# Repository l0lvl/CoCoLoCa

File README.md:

# CoCoLoCa - MC6847T1 VDG Conversion for CoCo 1 and 2
 
The **CoCoLoCa** allows installation of an MC6847T1/XC80652P in a Radio Shack Colour Computer 1 or 2

This is based on the work of Tony DiStefano as published in the October through December 1986 issues of Rainbow magazine. 

Over the course of two or three articles, Tony explains how to install the new VDG in the Colour Computer, and how to use switches to configure text mode.
This design attempts to cover both the installation and provide jumpers for the text mode settings.

The main PCB (assuming I've interpreted the instructions correctly and failed to make any mistakes) should let you substitute the new MC6847T1/XC80652P VDG in place of the old MC6847. This enables lower case character set (hence the name of this project) as well as a couple of different text mode options. The chip is rather hard to find, but since I have one I thought this would be fun project for #septandy this year.

The main PCB has two fly out lines that have to go to the SAM chip. 

The config plug is installed in place of a 74LS273 that must be removed from the motherboard.  I believe this reconfigures your Coco for some of the data and address pin changes on the new VDG. 

There is an optional SAMTAP board that just lets you easily remove the modification later.

Tony suggests that the wiring for the plug may require a different configuration for CoCo2 models, so expect to see more plugable boards here for those models if that turns out to be the case. I think he also mentioned prizes for sending him the various configuration maps and that he would publish them, but I've come up empty looking for such.

In any case, this design has not been tested so use at your own risk.

Happy #septandy 2022!

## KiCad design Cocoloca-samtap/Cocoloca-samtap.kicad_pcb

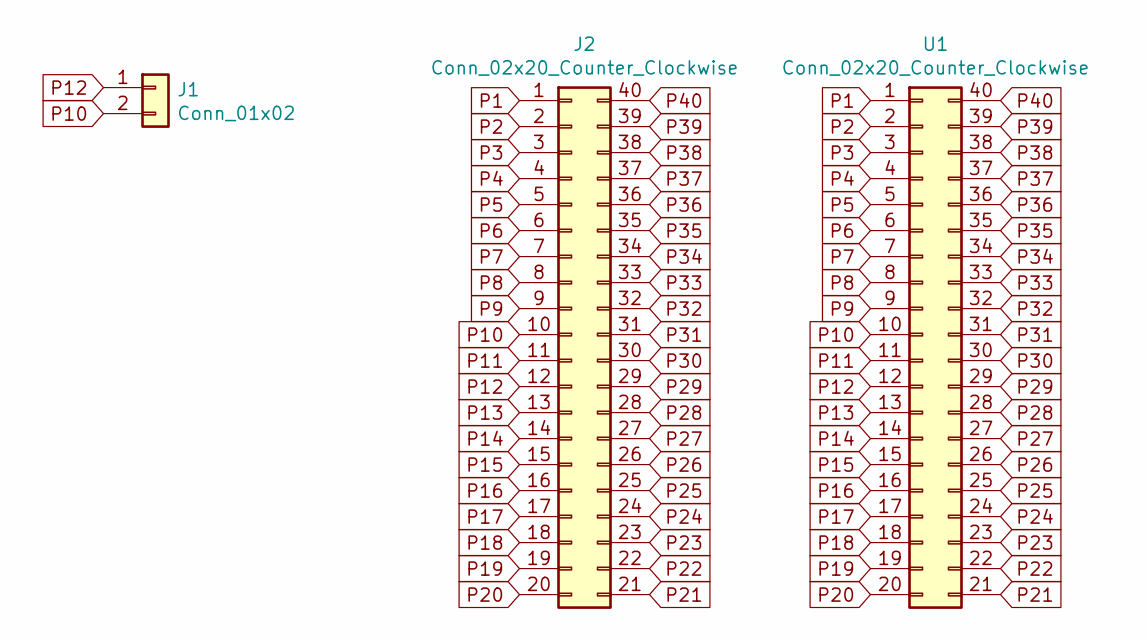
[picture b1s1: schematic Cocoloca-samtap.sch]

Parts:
J1: Conn_01x02; PinHeader_1x02_P2.54mm_Horizontal
J2: Conn_02x20_Counter_Clockwise; DIP-40_W15.24mm_LongPads
U1: Conn_02x20_Counter_Clockwise; DIP-40_W15.24mm_LongPads

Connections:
P1: J2.1, U1.1
P2: J2.2, U1.2
P3: J2.3, U1.3
P4: J2.4, U1.4
P5: J2.5, U1.5
P6: J2.6, U1.6
P7: J2.7, U1.7
P8: J2.8, U1.8
P9: J2.9, U1.9
P10: J1.2, J2.10, U1.10
P11: J2.11, U1.11
P12: J1.1, J2.12, U1.12
P13: J2.13, U1.13
P14: J2.14, U1.14
P15: J2.15, U1.15
P16: J2.16, U1.16
P17: J2.17, U1.17
P18: J2.18, U1.18
P19: J2.19, U1.19
P20: J2.20, U1.20
P21: J2.21, U1.21
P22: J2.22, U1.22
P23: J2.23, U1.23
P24: J2.24, U1.24
P25: J2.25, U1.25
P26: J2.26, U1.26
P27: J2.27, U1.27
P28: J2.28, U1.28
P29: J2.29, U1.29
P30: J2.30, U1.30
P31: J2.31, U1.31
P32: J2.32, U1.32
P33: J2.33, U1.33
P34: J2.34, U1.34
P35: J2.35, U1.35
P36: J2.36, U1.36
P37: J2.37, U1.37
P38: J2.38, U1.38
P39: J2.39, U1.39
P40: J2.40, U1.40

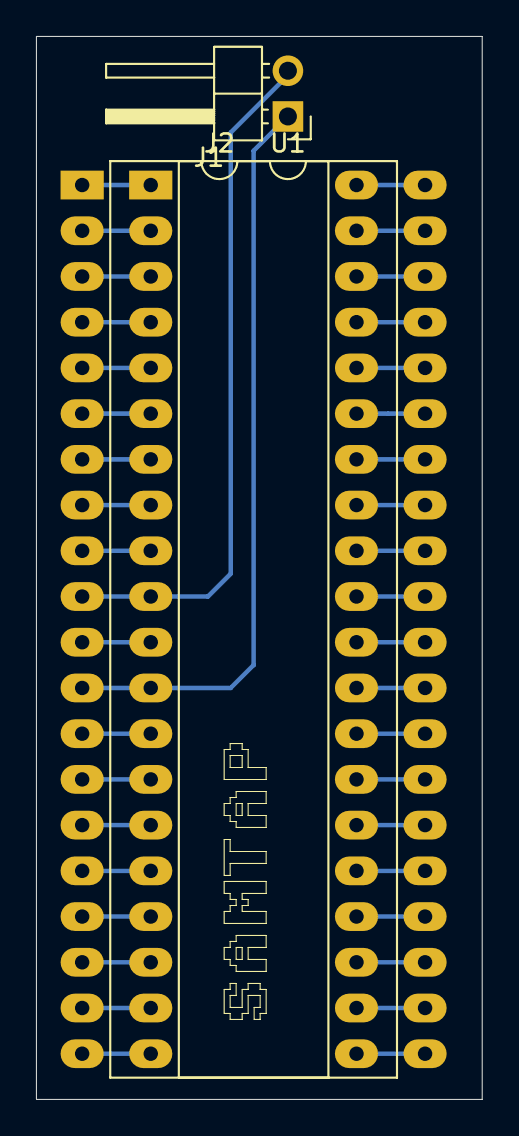
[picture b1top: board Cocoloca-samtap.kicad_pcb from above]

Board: 2 copper layers, 24.8 x 59.1 mm, 3 parts (0 on the bottom side), 40 nets.

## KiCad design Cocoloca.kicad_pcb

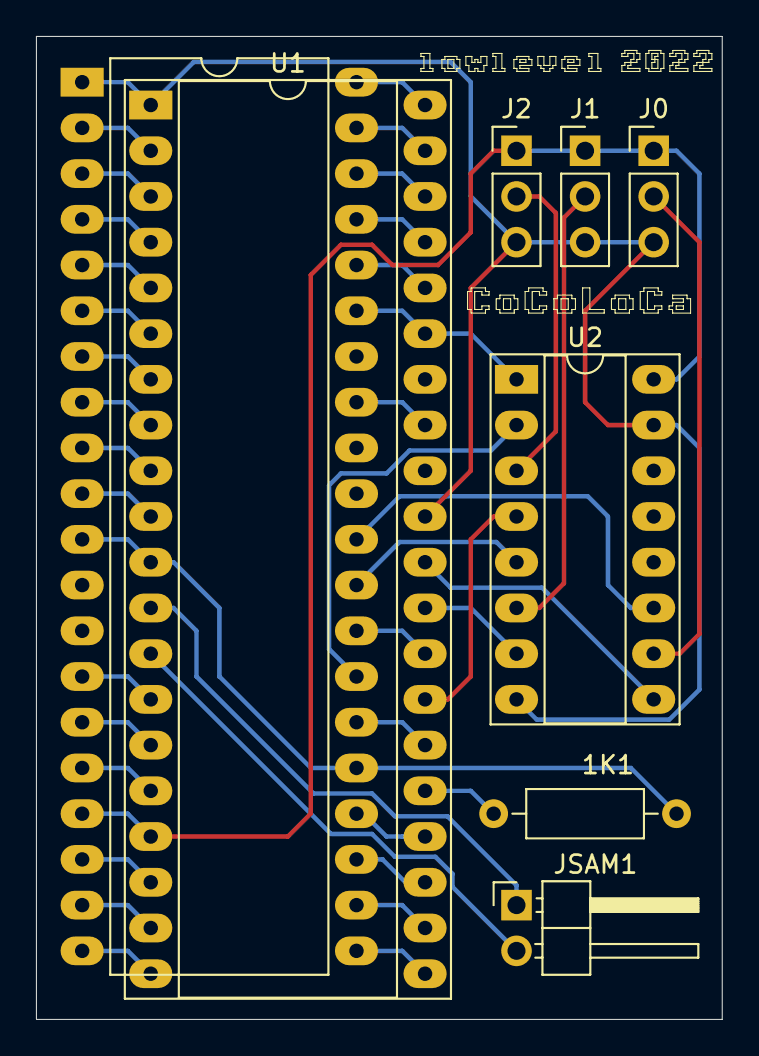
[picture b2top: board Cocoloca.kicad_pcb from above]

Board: 2 copper layers, 38.1 x 54.6 mm, 8 parts (0 on the bottom side), 43 nets.

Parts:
1K1: R1; R_Axial_DIN0207_L6.3mm_D2.5mm_P10.16mm_Horizontal
COCOVDG1: MC6847; DIP-40_W15.24mm_LongPads
J0, J1, J2: Conn_01x03_Male; PinHeader_1x03_P2.54mm_Vertical
JSAM1: Conn_01x02_Male; PinHeader_1x02_P2.54mm_Horizontal
U1: MC6847T1; DIP-40_W15.24mm_Socket_LongPads
U2: 74LS157; DIP-16_W7.62mm_Socket_LongPads

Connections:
GND: COCOVDG1.1, J0.3, J1.3, J2.3, U1.1, U1.31, U2.8, U2.15
unnamed: 1K1.1, U1.25
unnamed: COCOVDG1.27, U2.2
unnamed: COCOVDG1.29, U2.5
unnamed: COCOVDG1.30, U2.11
unnamed: U1.27, U2.4
unnamed: U1.29, U2.7
unnamed: U1.30, U2.9
S2: COCOVDG1.2, U1.2
S3: COCOVDG1.3, U1.3
S4: COCOVDG1.4, U1.4
S5: COCOVDG1.5, U1.5
S6: COCOVDG1.6, U1.6
S7: COCOVDG1.7, U1.7
S8: COCOVDG1.8, U1.8
S9: COCOVDG1.9, U1.9
S10: COCOVDG1.10, U1.10
S11: 1K1.2, COCOVDG1.11, COCOVDG1.25, U1.11
S14: COCOVDG1.14, U1.14
S15: COCOVDG1.15, U1.15
S16: COCOVDG1.16, U1.16
S18: COCOVDG1.18, U1.18
S19: COCOVDG1.19, U1.19
S20: COCOVDG1.20, U1.20
S21: COCOVDG1.21, U1.21
S22: COCOVDG1.22, U1.22
S23: COCOVDG1.23, U1.23
S24: COCOVDG1.24, U1.24
S26: COCOVDG1.26, U1.26
S28: COCOVDG1.28, U1.28
S33: COCOVDG1.33, U1.33
S35: COCOVDG1.35, U1.35, U2.1
S36: COCOVDG1.36, U1.36
S37: COCOVDG1.37, U1.37
S38: COCOVDG1.38, U1.38
S39: COCOVDG1.39, U1.39
S40: COCOVDG1.40, U1.40
SAM10: JSAM1.1, U1.12
SAM12: JSAM1.2, U1.13
TGM0: J0.2, U2.10
TGM1: J1.2, U2.6
TGM2: J2.2, U2.3
VCC: COCOVDG1.17, J0.1, J1.1, J2.1, U1.17, U2.16

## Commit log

2022-09-29 Initial check in
    KiCad Schematic and PCB's for MC6847TI Adapter and Config board for 74LS273 socket
2022-09-29 Update README.md
    Updated readme
2022-09-29 Update README.md
    further update to readme
2022-09-29 Update README.md
    Revised readme
2022-09-29 Gerbers cleaned up
    Added missing edge cuts for Coco1 plug. Added dxf graphic files and cleaned up gerber plots as per board house production specs.
2022-09-29 Added SAMTAP board
    Optional SAMTAP board to help make the modification easy to reverse. Readme also updated.
